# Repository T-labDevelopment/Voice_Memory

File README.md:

# Voice_Memory — v1試作資料とv2製造承認基準

**現在の製造・開発基準：v2（2026-11-11製造承認済み）**

| 版 | 位置付け | 参照 |
|---|---|---|
| **v1** | 旧試作・製造検証用の資料。費用計算は行わない | [v1専用ページ](releases/v1-prototype/README.md) |
| **v2** | **製造承認済み（ユーザー承認・2026-11-11）** | [v2製造承認記録](releases/v2-manufacturing-approved-2026-11-11/README.md) |
| v2技術 | 現行の回路・PCB・開発仕様 | [v2仕様書](development/v2/README.md) |
| v2費用 | v2のみ費用を管理。総額は未見積 | [開発費・必要仕様](development/v2/DEVELOPMENT_AND_COST_SCOPE_JA.md) |

## 製造データ

- **承認原本ZIP：** [`voicememory-2026-11-11_164201.zip`](hardware/source-archives/v2-baseline/voicememory-2026-11-11_164201.zip)
- **承認原本SHA-256：** `a64d1d4d439a141a7048c7fe233227507cebeaa69209cd91ddddc90118438c7a`
- **KiCad 10設計ファイル：** [`hardware/kicad/voicememory/`](hardware/kicad/voicememory/)
- **受領・検証証拠：** [v2基準ZIPの照合記録](hardware/reports/V2_BASELINE_RECEIPT_2026-11-11_JA.md)
- **製造承認：** プロジェクト責任者（ユーザー）の明示指示により承認済み。
- **ERC／DRC：** ユーザー側で実施済みと申告。正式検証レポート未収録、独立再実行は未実施であり、エラー0／警告0という個別結果の確認は未完了。

2026-11-10以前のECOレポートは過去のPCBに関する**履歴資料**であり、現行製造承認版に対する未解決不良の判定には使用しない。

## Git運用

- 現行開発ブランチ：`develop/v2`。
- [v2製造承認データ](releases/v2-manufacturing-approved-2026-11-11/README.md)は固定ZIPのハッシュで同定。設計変更は別コミットで扱う。
- `main` 統合、旧v1タグ改変、過去コミットの書換えは実施していない。
- [旧v1原本の受領・比較記録](hardware/reports/ECO_ZIP_RECEIPT_COMPARE_2026-11-11_JA.md)と[履歴バックアップ](history/README.md)は保管を維持する。

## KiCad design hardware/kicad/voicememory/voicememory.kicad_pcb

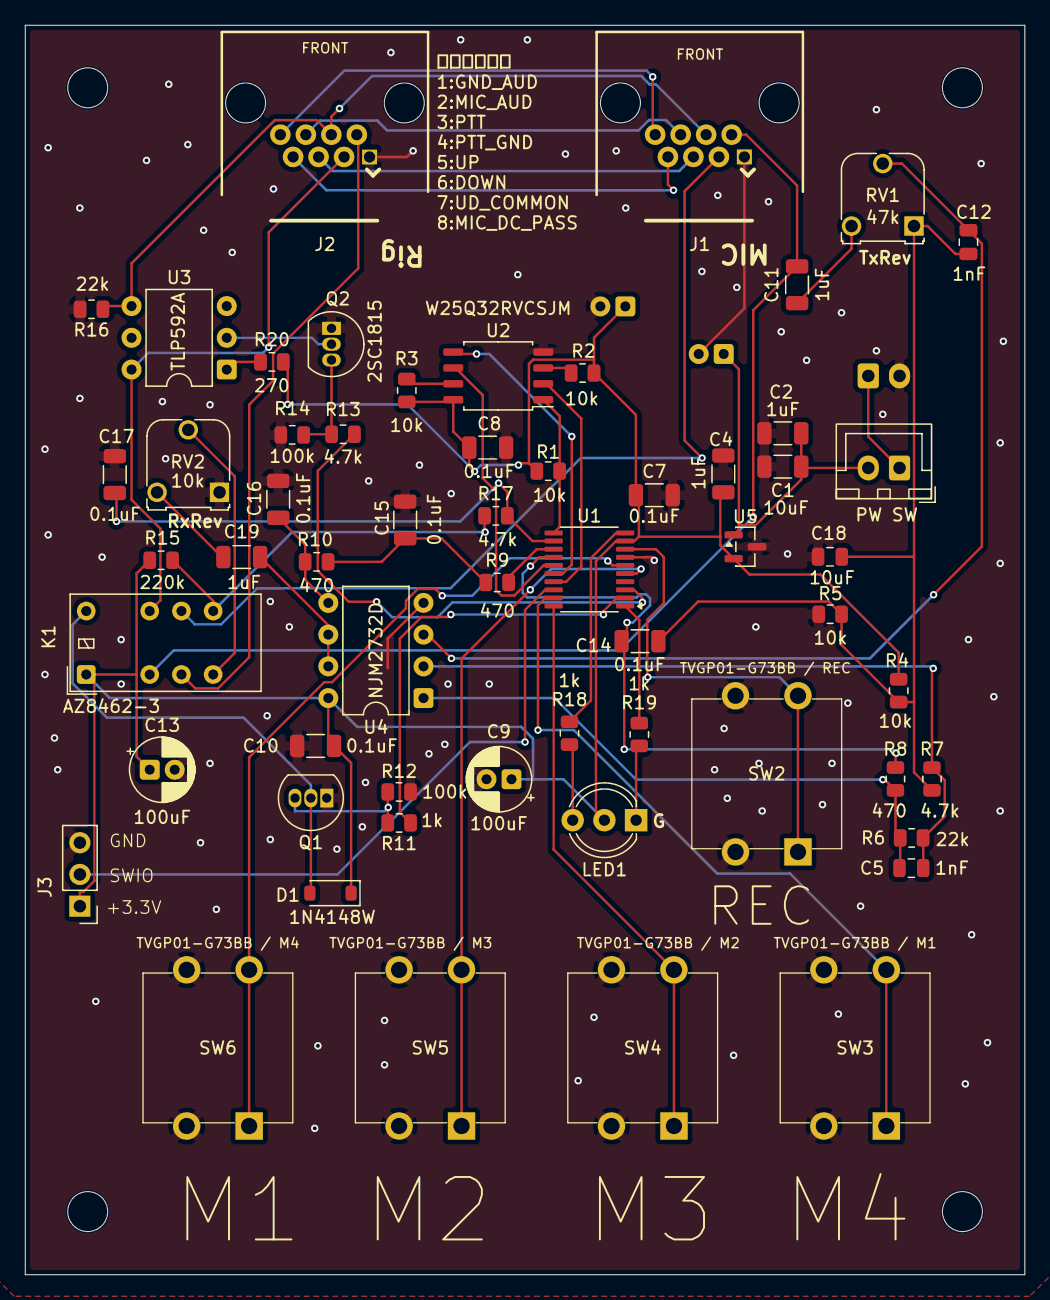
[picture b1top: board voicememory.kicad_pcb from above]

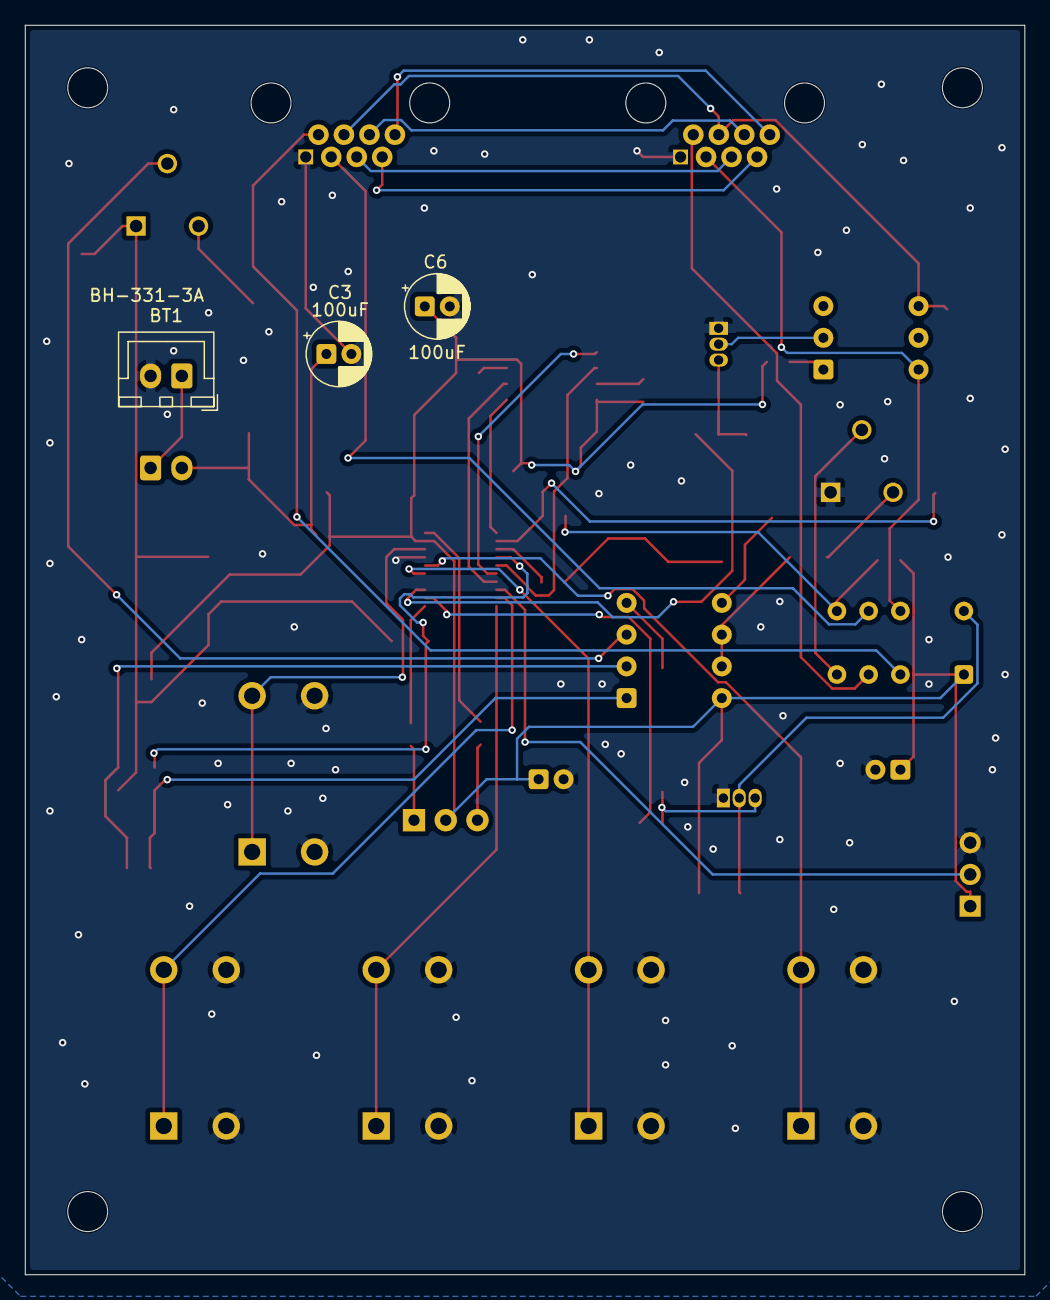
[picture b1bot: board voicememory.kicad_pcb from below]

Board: 2 copper layers, 80.0 x 100.0 mm, 61 parts (3 on the bottom side), 50 nets.

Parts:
BT1: BH-331-3A; JST_XH_B2B-XH-A_1x02_P2.50mm_Vertical
C1: 10uF; C_1206_3216Metric
C2, C4, C11, C19: 1uF; C_1206_3216Metric
C3, C6, C9, C13: 100uF; CP_Radial_D5.0mm_P2.00mm
C5, C12: 1nF; C_0805_2012Metric
C7, C8, C10, C14, C15, C16, C17: 0.1uF; C_1206_3216Metric
C18: 10uF; C_0805_2012Metric
D1: 1N4148W; D_SOD-123
J1: RJ45_8P8C MIC; RJ45_8P8C_THT_15.91x15.10
J2: RJ45_8P8C RIG; RJ45_8P8C_THT_15.91x15.10
J3: WCH-Link 3P; PinHeader_1x03_P2.54mm_Vertical
K1: AZ8462-3; Relay_DPDT_Kemet_EC2_NU
LED1: LT6CU7R; LED_D5.0mm-3
Q1: 2SC1815L-Y-T92; TO-92_Inline
Q2: 2SC1815; TO-92_Inline
R1, R2, R3, R4, R5: 10k; R_0805_2012Metric
R6, R16: 22k; R_0805_2012Metric
R7, R13, R17: 4.7k; R_0805_2012Metric
R8, R9, R10: 470; R_0805_2012Metric
R11, R18, R19: 1k; R_0805_2012Metric
R12, R14: 100k; R_0805_2012Metric
R15: 220k; R_0805_2012Metric
R20: 270; R_0805_2012Metric
RV1: 47k; Potentiometer_Runtron_RM-065_Vertical
RV2: 10k; Potentiometer_Runtron_RM-065_Vertical
SW1: CW-SB11KKFF; JST_XH_B2B-XH-A_1x02_P2.50mm_Vertical
SW2: TVGP01-G73BB / REC; SW_TVGP01_G73BB_12mm
SW3: TVGP01-G73BB / M1; SW_TVGP01_G73BB_12mm
SW4: TVGP01-G73BB / M2; SW_TVGP01_G73BB_12mm
SW5: TVGP01-G73BB / M3; SW_TVGP01_G73BB_12mm
SW6: TVGP01-G73BB / M4; SW_TVGP01_G73BB_12mm
U1: CH32V003F4P6; TSSOP-20_4.4x6.5mm_P0.65mm
U2: W25Q32RVCSJM; SOP-8_5.28x5.23mm_P1.27mm
U3: TLP592A; DIP-6_W7.62mm
U4: NJM2732D; DIP-8_W7.62mm
U5: AP7333-33SAG; SOT-23

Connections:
+3V3: C4.1, C6.1, C7.1, C8.1, C9.1, C10.1, C13.1, D1.1 (K), J3.1, K1.1 (COIL+), LED1.2 (A_COMMON), R1.2, R2.2, R3.2, R4.1, R15.1, R20.1, U1.9 (VDD), U2.8 (VCC), U4.8 (V+), U5.2 (OUT)
AQV_LED_A: R20.2, U3.1 (A)
AQV_LED_K: Q2.2 (C), U3.2 (K)
AUDIO_ADC: C14.1, R8.2, U1.14 (PC4)
AUDIO_PWM: R9.1, U1.13 (PC3)
AUTO_PTT_EN: R13.1, U1.3 (PD6)
FLASH_CS: R1.1, U1.11 (PC1), U2.1 (/CS)
FLASH_HOLD_N: R3.1, U2.7 (/HOLD/IO3)
FLASH_WP_N: R2.1, U2.3 (/WP/IO2)
GND_AUD: BT1.2 (-), C1.2, C2.2, C3.2, C4.2, C6.2, C7.2, C8.2, C9.2, C10.2, C13.2, C15.2, C16.2, C17.2, C18.2, J1.1, J2.1, J3.3, Q1.1 (E), Q2.1 (E), R5.2, R12.2, R14.2, R16.2, RV2.1, SW2.2, SW3.2, SW4.2, SW5.2, SW6.2, U1.7 (VSS), U2.4 (GND), U4.4 (V-), U5.3 (GND)
LED_G: R19.2, U1.1 (PD4)
LED_G_K: LED1.1 (K_YG), R19.1
LED_R: R18.2, U1.10 (PC0)
LED_R_K: LED1.3 (K_RED), R18.1
MIC_AUDIO: C11.1, J1.2, K1.3 (A_NC)
MIC_DC_PASS: J1.8, J2.8
MIC_DOWN: J1.6, J2.6
MIC_PTT: J1.3, K1.9 (B_COM)
MIC_UP: J1.5, J2.5
PLAY_AC: C19.2, RV2.3
PLAY_BIASED: C19.1, U4.6 (-), U4.7
PLAY_OUT: K1.5 (A_NO), RV2.2
PTT_GND: J1.4, J2.4, R16.1, U3.4 (DRAIN_D1)
PTT_SENSE_LOCAL: K1.8 (B_NO), R15.2, R17.1
PTT_SENSE_MCU: C17.1, R17.2, U1.12 (PC2)
PWM_F1: C15.1, R9.2, R10.1
PWM_F2: C16.1, R10.2, U4.5 (+)
Q1_BASE: Q1.3 (B), R11.2, R12.1
Q2_BASE: Q2.3 (B), R13.2, R14.1
REC_AC: C11.2, RV1.3
REC_AMP_OUT: C5.1, R6.1, R8.1, U4.1
REC_FB: C5.2, R6.2, R7.1, U4.2 (-)
REC_LEVEL: C12.1, RV1.2, U4.3 (+)
RELAY_COIL_LOW: D1.2 (A), K1.12 (COIL-), Q1.2 (C)
RELAY_EN: R11.1, U1.2 (PD5)
RIG_AUDIO: J2.2, K1.4 (A_COM)
RIG_PTT: J2.3, K1.10 (B_NC), U3.6 (DRAIN_D2)
SPI_MISO: U1.17 (PC7), U2.2 (DO/IO1)
SPI_MOSI: U1.16 (PC6), U2.5 (DI/IO0)
SPI_SCK: U1.15 (PC5), U2.6 (CLK)
SWIO: J3.2, U1.18 (PD1/SWIO)
SW_M1_N: SW3.1, U1.19 (PD2)
SW_M2_N: SW4.1, U1.20 (PD3)
SW_M3_N: SW5.1, U1.5 (PA1)
SW_M4_N: SW6.1, U1.6 (PA2)
SW_REC_N: SW2.1, U1.8 (PD0)
UD_COMMON: J1.7, J2.7
VBAT_RAW: BT1.1 (+), SW1.1 (A)
VBAT_SW: C1.1, C2.1, C3.1, SW1.2 (B), U5.1 (IN)
VREF: C12.2, C14.2, C18.1, R4.2, R5.1, R7.2, RV1.1
